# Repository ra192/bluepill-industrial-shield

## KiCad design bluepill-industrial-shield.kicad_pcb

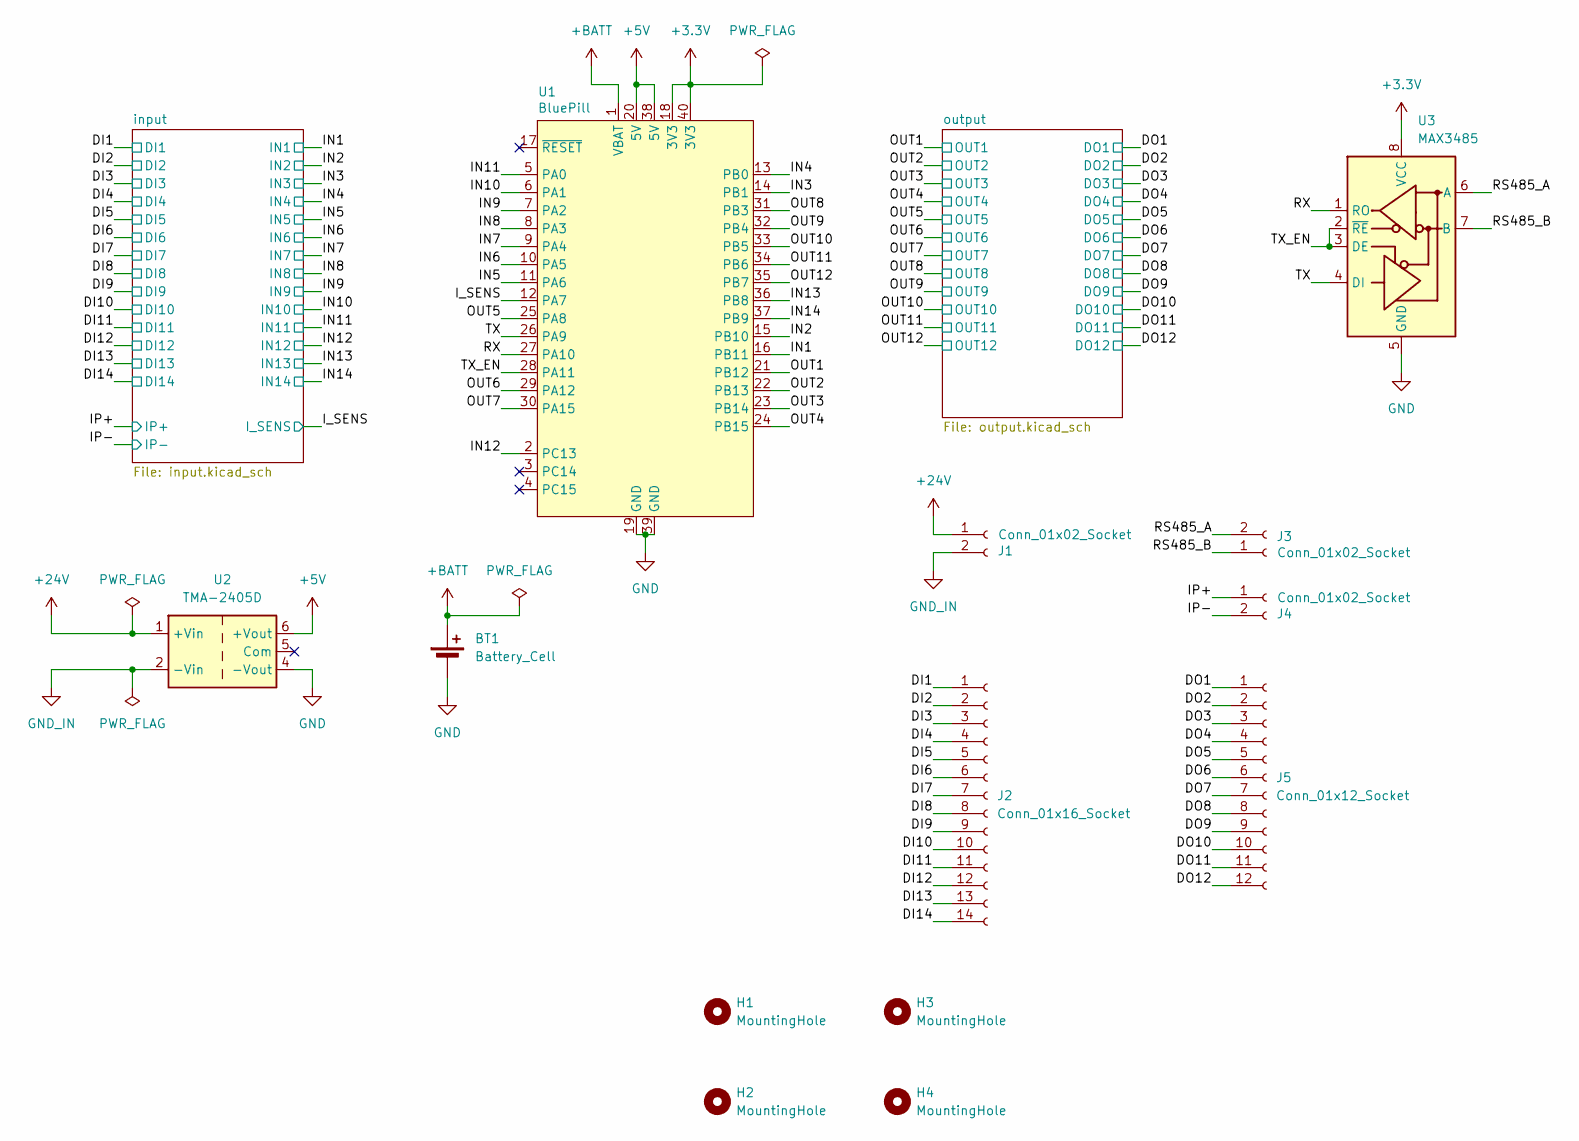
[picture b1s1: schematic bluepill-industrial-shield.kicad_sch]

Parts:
BT1: Battery_Cell; Battery_Panasonic_CR1220-VCN_Vertical_CircularHoles
H1, H2, H3, H4: MountingHole; MountingHole_3.2mm_M3
J1, J3, J4: Conn_01x02_Socket; PhoenixContact_MCV_1,5_2-G-3.5_1x02_P3.50mm_Vertical
J2: Conn_01x16_Socket; PhoenixContact_MCV_1,5_14-G-3.5_1x14_P3.50mm_Vertical
J5: Conn_01x12_Socket; PhoenixContact_MCV_1,5_12-G-3.5_1x12_P3.50mm_Vertical
U1: BluePill; BlackPill
U2: TMA-2405D; Converter_DCDC_TRACO_TMA-15xxD_24xxD_Dual_THT
U3: MAX3485; SOIC-8_3.9x4.9mm_P1.27mm

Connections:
+3.3V: U1.18 (3V3), U1.40 (3V3), U3.8 (VCC)
+5V: U1.20 (5V), U1.38 (5V), U2.6 (+Vout); also elsewhere on the board
+24V: J1.1, U2.1 (+Vin); also elsewhere on the board
+BATT: BT1.1 (+), U1.1 (VBAT)
/DI1: J2.1; also elsewhere on the board
/DI2: J2.2; also elsewhere on the board
/DI3: J2.3; also elsewhere on the board
/DI4: J2.4; also elsewhere on the board
/DI5: J2.5; also elsewhere on the board
/DI6: J2.6; also elsewhere on the board
/DI7: J2.7; also elsewhere on the board
/DI8: J2.8; also elsewhere on the board
/DI9: J2.9; also elsewhere on the board
/DI10: J2.10; also elsewhere on the board
/DI11: J2.11; also elsewhere on the board
/DI12: J2.12; also elsewhere on the board
/DI13: J2.13; also elsewhere on the board
/DI14: J2.14; also elsewhere on the board
/DO1: J5.1; also elsewhere on the board
/DO2: J5.2; also elsewhere on the board
/DO3: J5.3; also elsewhere on the board
/DO4: J5.4; also elsewhere on the board
/DO5: J5.5; also elsewhere on the board
/DO6: J5.6; also elsewhere on the board
/DO7: J5.7; also elsewhere on the board
/DO8: J5.8; also elsewhere on the board
/DO9: J5.9; also elsewhere on the board
/DO10: J5.10; also elsewhere on the board
/DO11: J5.11; also elsewhere on the board
/DO12: J5.12; also elsewhere on the board
/IN1: U1.16 (PB11); also elsewhere on the board
/IN2: U1.15 (PB10); also elsewhere on the board
/IN3: U1.14 (PB1); also elsewhere on the board
/IN4: U1.13 (PB0); also elsewhere on the board
/IN5: U1.11 (PA6); also elsewhere on the board
/IN6: U1.10 (PA5); also elsewhere on the board
/IN7: U1.9 (PA4); also elsewhere on the board
/IN8: U1.8 (PA3); also elsewhere on the board
/IN9: U1.7 (PA2); also elsewhere on the board
/IN10: U1.6 (PA1); also elsewhere on the board
/IN11: U1.5 (PA0); also elsewhere on the board
/IN12: U1.2 (PС13); also elsewhere on the board
/IN13: U1.36 (PB8); also elsewhere on the board
/IN14: U1.37 (PB9); also elsewhere on the board
/IP+: J4.1; also elsewhere on the board
/IP-: J4.2; also elsewhere on the board
/I_SENS: U1.12 (PA7); also elsewhere on the board
/OUT1: U1.21 (PB12); also elsewhere on the board
/OUT2: U1.22 (PB13); also elsewhere on the board
/OUT3: U1.23 (PB14); also elsewhere on the board
/OUT4: U1.24 (PB15); also elsewhere on the board
/OUT5: U1.25 (PA8); also elsewhere on the board
/OUT6: U1.29 (PA12); also elsewhere on the board
/OUT7: U1.30 (PA15); also elsewhere on the board
/OUT8: U1.31 (PB3); also elsewhere on the board
/OUT9: U1.32 (PB4); also elsewhere on the board
/OUT10: U1.33 (PB5); also elsewhere on the board
/OUT11: U1.34 (PB6); also elsewhere on the board
/OUT12: U1.35 (PB7); also elsewhere on the board
/RS485_A: J3.2, U3.6 (A)
/RS485_B: J3.1, U3.7 (B)
/RX: U1.27 (PA10), U3.1 (RO)
/TX: U1.26 (PA9), U3.4 (DI)
/TX_EN: U1.28 (PA11), U3.2 (~RE), U3.3 (DE)
GND: BT1.2 (-), U1.19 (GND), U1.39 (GND), U2.4 (-Vout), U3.5 (GND); also elsewhere on the board
GND_IN: J1.2, U2.2 (-Vin); also elsewhere on the board

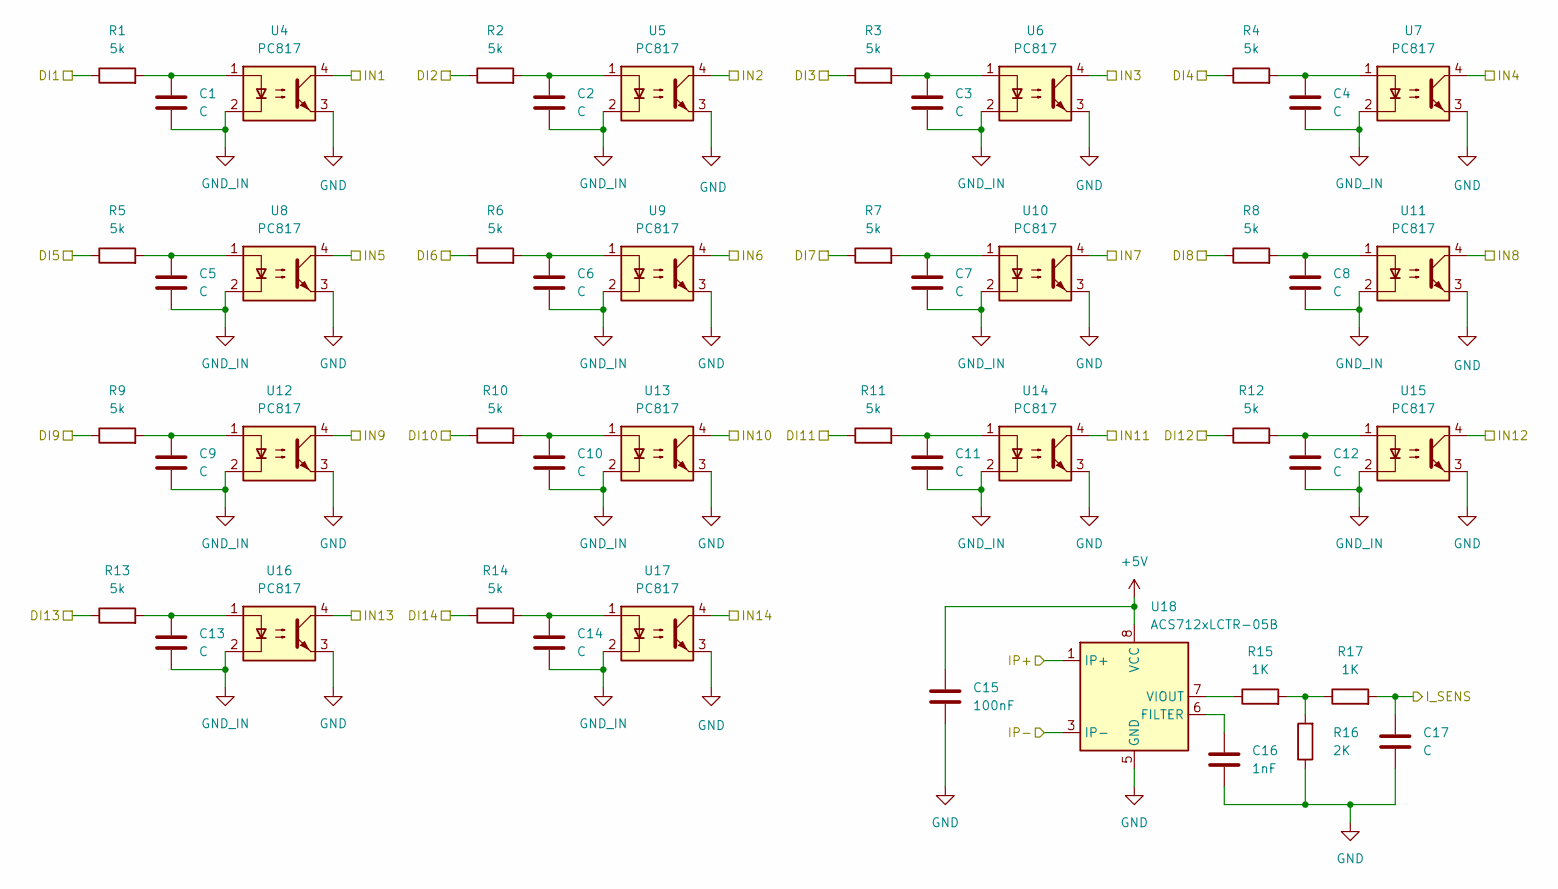
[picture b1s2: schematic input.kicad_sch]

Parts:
C1, C2, C3, C4, C5, C6, C7, C8, C9, C10, C11, C12, C13, C14: C; C_0805_2012Metric_Pad1.18x1.45mm_HandSolder
C15: 100nF; C_0805_2012Metric
C16: 1nF; C_0805_2012Metric
C17: C; C_0805_2012Metric
R1, R2, R3, R4, R5, R6, R7, R8, R9, R10, R11, R12, R13, R14: 5k; R_0805_2012Metric_Pad1.20x1.40mm_HandSolder
R15, R17: 1K; R_0805_2012Metric_Pad1.20x1.40mm_HandSolder
R16: 2K; R_0805_2012Metric_Pad1.20x1.40mm_HandSolder
U4, U5, U6, U7, U8, U9, U10, U11, U12, U13, U14, U15, U16, U17: PC817; DIP-4_W7.62mm
U18: ACS712xLCTR-05B; SOIC-8_3.9x4.9mm_P1.27mm

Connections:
+5V: C15.1, U18.8 (VCC); also elsewhere on the board
/DI1: R1.1; also elsewhere on the board
/DI2: R2.1; also elsewhere on the board
/DI3: R3.1; also elsewhere on the board
/DI4: R4.1; also elsewhere on the board
/DI5: R5.1; also elsewhere on the board
/DI6: R6.1; also elsewhere on the board
/DI7: R7.1; also elsewhere on the board
/DI8: R8.1; also elsewhere on the board
/DI9: R9.1; also elsewhere on the board
/DI10: R10.1; also elsewhere on the board
/DI11: R11.1; also elsewhere on the board
/DI12: R12.1; also elsewhere on the board
/DI13: R13.1; also elsewhere on the board
/DI14: R14.1; also elsewhere on the board
/IN1: U4.4; also elsewhere on the board
/IN2: U5.4; also elsewhere on the board
/IN3: U6.4; also elsewhere on the board
/IN4: U7.4; also elsewhere on the board
/IN5: U8.4; also elsewhere on the board
/IN6: U9.4; also elsewhere on the board
/IN7: U10.4; also elsewhere on the board
/IN8: U11.4; also elsewhere on the board
/IN9: U12.4; also elsewhere on the board
/IN10: U13.4; also elsewhere on the board
/IN11: U14.4; also elsewhere on the board
/IN12: U15.4; also elsewhere on the board
/IN13: U16.4; also elsewhere on the board
/IN14: U17.4; also elsewhere on the board
/IP+: U18.1 (IP+), U18.2 (IP+); also elsewhere on the board
/IP-: U18.3 (IP-), U18.4 (IP-); also elsewhere on the board
/I_SENS: C17.1, R17.2; also elsewhere on the board
GND: C15.2, C16.2, C17.2, R16.1, U4.3, U5.3, U6.3, U7.3, U8.3, U9.3, U10.3, U11.3, U12.3, U13.3, U14.3, U15.3, U16.3, U17.3, U18.5 (GND); also elsewhere on the board
GND_IN: C1.2, C2.2, C3.2, C4.2, C5.2, C6.2, C7.2, C8.2, C9.2, C10.2, C11.2, C12.2, C13.2, C14.2, U4.2, U5.2, U6.2, U7.2, U8.2, U9.2, U10.2, U11.2, U12.2, U13.2, U14.2, U15.2, U16.2, U17.2; also elsewhere on the board
unnamed: C1.1, R1.2, U4.1
unnamed: C2.1, R2.2, U5.1
unnamed: C3.1, R3.2, U6.1
unnamed: C4.1, R4.2, U7.1
unnamed: C5.1, R5.2, U8.1
unnamed: C6.1, R6.2, U9.1
unnamed: C7.1, R7.2, U10.1
unnamed: C8.1, R8.2, U11.1
unnamed: C9.1, R9.2, U12.1
unnamed: C10.1, R10.2, U13.1
unnamed: C11.1, R11.2, U14.1
unnamed: C12.1, R12.2, U15.1
unnamed: C13.1, R13.2, U16.1
unnamed: C14.1, R14.2, U17.1
unnamed: R15.2, R16.2, R17.1
unnamed: C16.1, U18.6 (FILTER)
unnamed: R15.1, U18.7 (VIOUT)

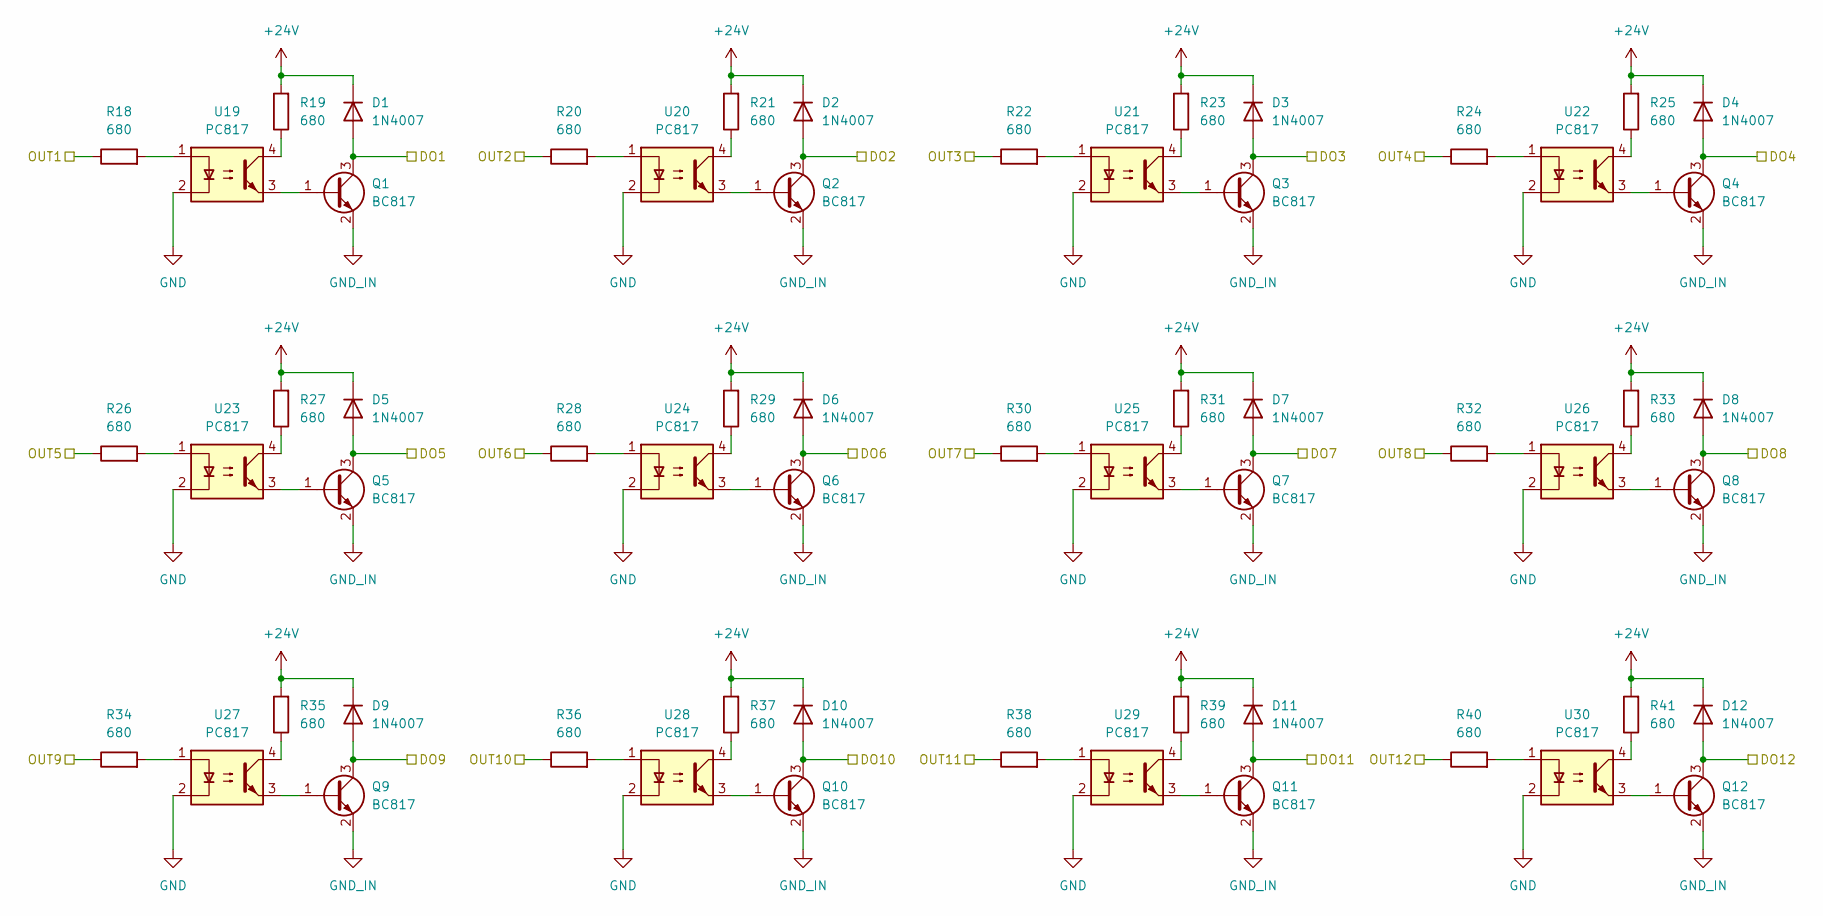
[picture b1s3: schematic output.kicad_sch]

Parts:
D1, D2, D3, D4, D5, D6, D7, D8, D9, D10, D11, D12: 1N4007; D_SMA_Handsoldering
Q1, Q2, Q3, Q4, Q5, Q6, Q7, Q8, Q9, Q10, Q11, Q12: BC817; SOT-23
R18, R19, R20, R21, R22, R23, R24, R25, R26, R27, R28, R29, R30, R31, R32, R33, R34, R35, R36, R37, R38, R39, R40, R41: 680; R_0805_2012Metric_Pad1.20x1.40mm_HandSolder
U19, U20, U21, U22, U23, U24, U25, U26, U27, U28, U29, U30: PC817; DIP-4_W7.62mm

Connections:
+24V: D1.1 (K), D2.1 (K), D3.1 (K), D4.1 (K), D5.1 (K), D6.1 (K), D7.1 (K), D8.1 (K), D9.1 (K), D10.1 (K), D11.1 (K), D12.1 (K), R19.2, R21.2, R23.2, R25.2, R27.2, R29.2, R31.2, R33.2, R35.2, R37.2, R39.2, R41.2; also elsewhere on the board
/DO1: D1.2 (A), Q1.3 (C); also elsewhere on the board
/DO2: D2.2 (A), Q2.3 (C); also elsewhere on the board
/DO3: D3.2 (A), Q3.3 (C); also elsewhere on the board
/DO4: D4.2 (A), Q4.3 (C); also elsewhere on the board
/DO5: D5.2 (A), Q5.3 (C); also elsewhere on the board
/DO6: D6.2 (A), Q6.3 (C); also elsewhere on the board
/DO7: D7.2 (A), Q7.3 (C); also elsewhere on the board
/DO8: D8.2 (A), Q8.3 (C); also elsewhere on the board
/DO9: D9.2 (A), Q9.3 (C); also elsewhere on the board
/DO10: D10.2 (A), Q10.3 (C); also elsewhere on the board
/DO11: D11.2 (A), Q11.3 (C); also elsewhere on the board
/DO12: D12.2 (A), Q12.3 (C); also elsewhere on the board
/OUT1: R18.1; also elsewhere on the board
/OUT2: R20.1; also elsewhere on the board
/OUT3: R22.1; also elsewhere on the board
/OUT4: R24.1; also elsewhere on the board
/OUT5: R26.1; also elsewhere on the board
/OUT6: R28.1; also elsewhere on the board
/OUT7: R30.1; also elsewhere on the board
/OUT8: R32.1; also elsewhere on the board
/OUT9: R34.1; also elsewhere on the board
/OUT10: R36.1; also elsewhere on the board
/OUT11: R38.1; also elsewhere on the board
/OUT12: R40.1; also elsewhere on the board
GND: U19.2, U20.2, U21.2, U22.2, U23.2, U24.2, U25.2, U26.2, U27.2, U28.2, U29.2, U30.2; also elsewhere on the board
GND_IN: Q1.2 (E), Q2.2 (E), Q3.2 (E), Q4.2 (E), Q5.2 (E), Q6.2 (E), Q7.2 (E), Q8.2 (E), Q9.2 (E), Q10.2 (E), Q11.2 (E), Q12.2 (E); also elsewhere on the board
unnamed: Q1.1 (B), U19.3
unnamed: Q2.1 (B), U20.3
unnamed: Q3.1 (B), U21.3
unnamed: Q4.1 (B), U22.3
unnamed: Q5.1 (B), U23.3
unnamed: Q6.1 (B), U24.3
unnamed: Q7.1 (B), U25.3
unnamed: Q8.1 (B), U26.3
unnamed: Q9.1 (B), U27.3
unnamed: Q10.1 (B), U28.3
unnamed: Q11.1 (B), U29.3
unnamed: Q12.1 (B), U30.3
unnamed: R18.2, U19.1
unnamed: R19.1, U19.4
unnamed: R20.2, U20.1
unnamed: R21.1, U20.4
unnamed: R22.2, U21.1
unnamed: R23.1, U21.4
unnamed: R24.2, U22.1
unnamed: R25.1, U22.4
unnamed: R26.2, U23.1
unnamed: R27.1, U23.4
unnamed: R28.2, U24.1
unnamed: R29.1, U24.4
unnamed: R30.2, U25.1
unnamed: R31.1, U25.4
unnamed: R32.2, U26.1
unnamed: R33.1, U26.4
unnamed: R34.2, U27.1
unnamed: R35.1, U27.4
unnamed: R36.2, U28.1
unnamed: R37.1, U28.4
unnamed: R38.2, U29.1
unnamed: R39.1, U29.4
unnamed: R40.2, U30.1
unnamed: R41.1, U30.4

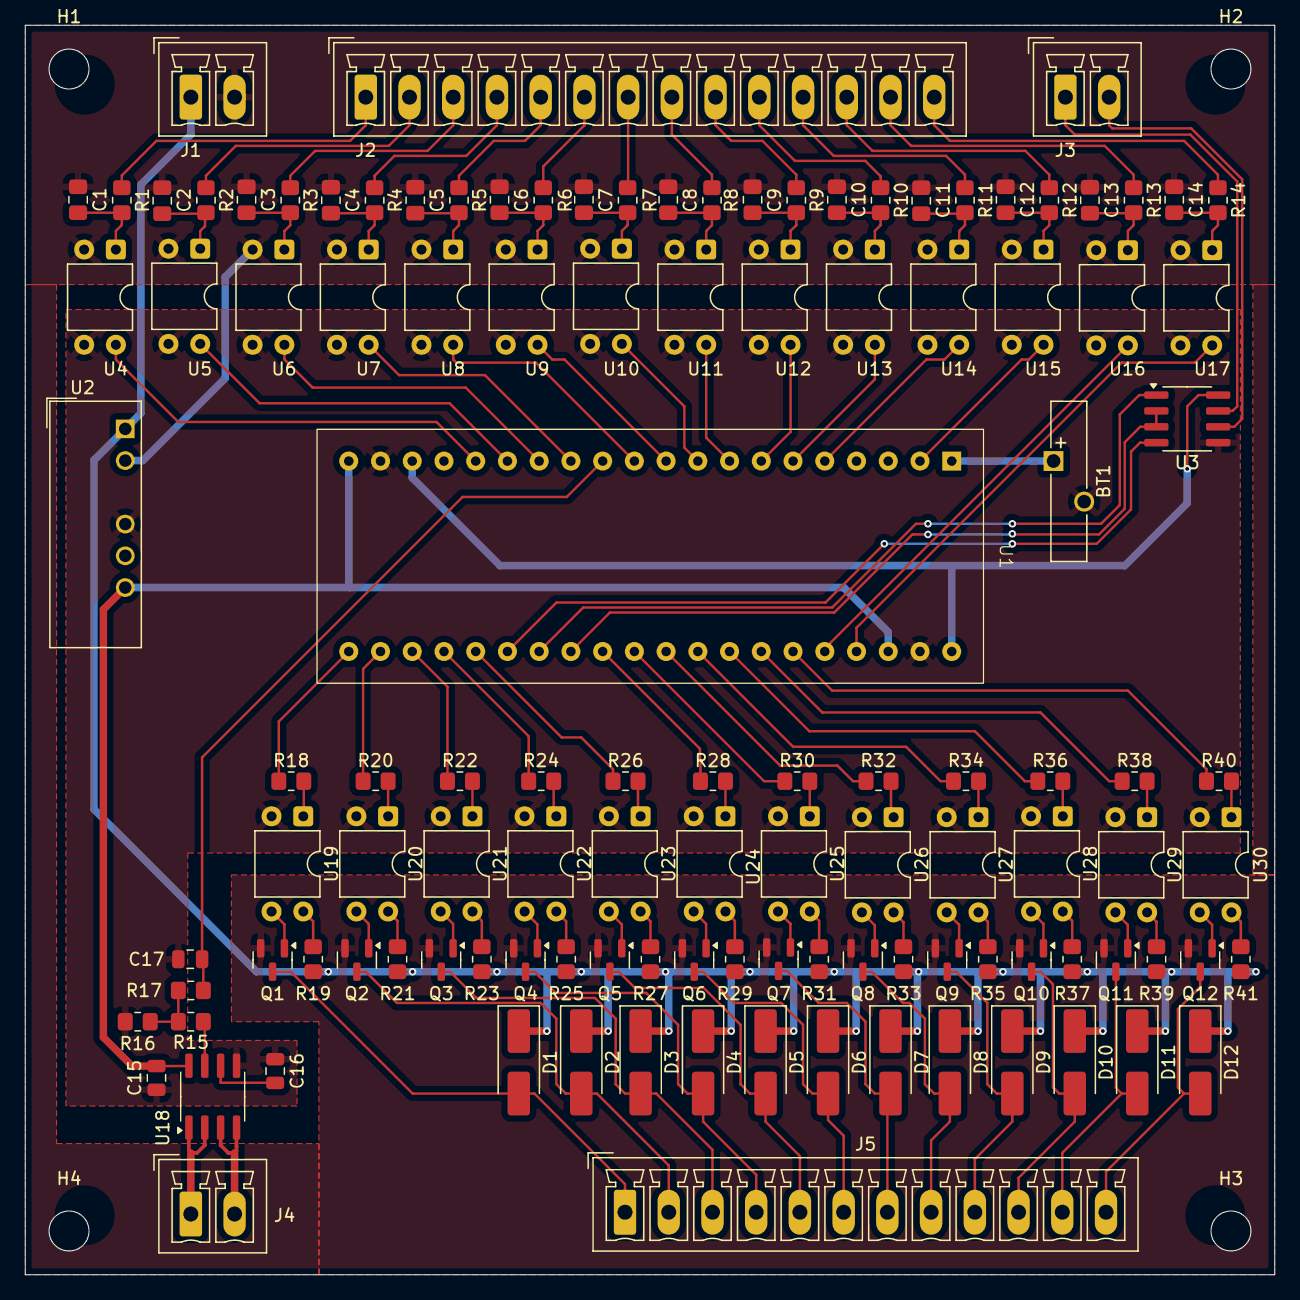
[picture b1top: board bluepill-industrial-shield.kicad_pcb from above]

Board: 2 copper layers, 100.0 x 100.0 mm, 122 parts (0 on the bottom side), 119 nets.

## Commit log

2025-01-26 trace pcb
2025-01-26 add battery
2025-03-02 update to kicad 9
